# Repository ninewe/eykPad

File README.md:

# eykPad

<br><br>

<b>A multifunctional pad!</b>

This can be used for a timer, a sequence memory game, and other fun stuff!

This project is a compact PCB to play minigames with basically just LEDS and a 7-segment display, such as memory games. It can also act as a productive tool, such as the pomodoro timer. This project consists of 30 LEDs, (a 5 by 6 LED matrix). I used multiplexing to save GPIO pins.

It also has a 7 segment display, which is useful for displaying numbers, and that also expands the ideas of games I can make. I kept the buttons compact and minimal. There are only three buttons, where the main function of each of the buttons are: (go right), (switch color to pick), and (enter). This makes picking each light from the 30 LED way easier. 

# eykPad – bill of materials

> [!NOTE]
> This parts list is mirrored from [Half Life](https://halflife.hackclub.com). Editing it here will not change the platform's copy, and the next sync overwrites this file.

| Week | Tier | Parts funding |
| --- | --- | --- |
| Week 1 | Tier 1 | $30.00 |

| Part | What it's for | Qty | Unit | Total | Vendor |
| --- | --- | --- | --- | --- | --- |
| [150080RS75000](https://www.digikey.com/en/products/detail/w-rth-elektronik/150080RS75000/4489918?gclsrc=aw.ds&gad_source=1&gad_campaignid=20228387720&gbraid=0AAAAADrbLliBca_8CoGRREvYeSftxtPPf&gclid=Cj0KCQjwuJLWBhD_ARIsAIBcRUyE15Ih_jkTIqsu-BNJK-R_mNFNQNt-TY-f5ciIsWRtXfK5UMoC-bQaAiLSEALw_wcB) | Outputs of this project. (Red LED) | 12 | $0.19 | $2.28 | [DigiKey](https://www.digikey.com/en/products/detail/w-rth-elektronik/150080RS75000/4489918?gclsrc=aw.ds&gad_source=1&gad_campaignid=20228387720&gbraid=0AAAAADrbLliBca_8CoGRREvYeSftxtPPf&gclid=Cj0KCQjwuJLWBhD_ARIsAIBcRUyE15Ih_jkTIqsu-BNJK-R_mNFNQNt-TY-f5ciIsWRtXfK5UMoC-bQaAiLSEALw_wcB) |
| [150080BS75000](https://www.digikey.com/en/products/detail/würth-elektronik/150080BS75000/4489912?s=N4IgTCBcDaIIwFYAMSAcSBCBlA7MlIAugL5A) | Outputs of this project. (Blue LED) | 12 | $0.19 | $2.28 | [DigiKey](https://www.digikey.com/en/products/detail/würth-elektronik/150080BS75000/4489912?s=N4IgTCBcDaIIwFYAMSAcSBCBlA7MlIAugL5A) |
| [150080YS75000](https://www.digikey.com/en/products/detail/würth-elektronik/150080YS75000/4489927?s=N4IgTCBcDaIIwFYAMSAcSCaBlA7MlIAugL5A) | Outputs of this project. (Yellow LED) | 12 | $0.19 | $2.28 | [DigiKey](https://www.digikey.com/en/products/detail/würth-elektronik/150080YS75000/4489927?s=N4IgTCBcDaIIwFYAMSAcSCaBlA7MlIAugL5A) |
| [SC0915](https://www.digikey.com/en/products/detail/raspberry-pi/SC0915/13624793) | The microcontroller. (Raspberry Pi Pico) | 1 | $4.59 | $4.59 | [DigiKey](https://www.digikey.com/en/products/detail/raspberry-pi/SC0915/13624793) |
| [B3FS-1000P](https://www.digikey.com/en/products/detail/aratas-formerly-omron-components/B3FS-1000P/277812) | Inputs of this project. (The buttons) | 3 | $0.75 | $2.25 | [DigiKey](https://www.digikey.com/en/products/detail/aratas-formerly-omron-components/B3FS-1000P/277812) |
| [RC0603FR-10330RL](https://www.digikey.com/en/products/detail/yageo/rc0603fr-10330rl/13694144?_gl=1*120rrj8*_up*MQ..*_gs*MQ..&gclid=Cj0KCQjwxKfWBhDkARIsAMKwkNawzWwHylZYBSNY6BOOnOnXhfwnokVGLYxYg4FlJP0YA3B5n22bPJ0aAlVSEALw_wcB&gclsrc=aw.ds&gbraid=0AAAAADrbLlhJyPxw7Auh62ErySqGjBCvJ) | Resistors for this LED. (for RED, 330 OHMS) | 10 | $0.03 | $0.30 | [DigiKey](https://www.digikey.com/en/products/detail/yageo/rc0603fr-10330rl/13694144?_gl=1*120rrj8*_up*MQ..*_gs*MQ..&gclid=Cj0KCQjwxKfWBhDkARIsAMKwkNawzWwHylZYBSNY6BOOnOnXhfwnokVGLYxYg4FlJP0YA3B5n22bPJ0aAlVSEALw_wcB&gclsrc=aw.ds&gbraid=0AAAAADrbLlhJyPxw7Auh62ErySqGjBCvJ) |
| [LTS-6960HR](https://www.digikey.com/en/products/detail/liteon/LTS-6960HR/3199487) | Outputs of this project. (7 segment display) | 1 | $1.82 | $1.82 | [DigiKey](https://www.digikey.com/en/products/detail/liteon/LTS-6960HR/3199487) |
| [RC0603FR-10300RL](https://www.digikey.com/en/products/detail/yageo/RC0603FR-10300RL/14008461?gclsrc=aw.ds&gad_source=1&gad_campaignid=17335707486&gbraid=0AAAAADrbLlhJyPxw7Auh62ErySqGjBCvJ&gclid=Cj0KCQjwxKfWBhDkARIsAMKwkNawzWwHylZYBSNY6BOOnOnXhfwnokVGLYxYg4FlJP0YA3B5n22bPJ0aAlVSEALw_wcB) | Resistors for this LED. (for YELLOW, 300 OHMS) | 10 | $0.03 | $0.30 | [DigiKey](https://www.digikey.com/en/products/detail/yageo/RC0603FR-10300RL/14008461?gclsrc=aw.ds&gad_source=1&gad_campaignid=17335707486&gbraid=0AAAAADrbLlhJyPxw7Auh62ErySqGjBCvJ&gclid=Cj0KCQjwxKfWBhDkARIsAMKwkNawzWwHylZYBSNY6BOOnOnXhfwnokVGLYxYg4FlJP0YA3B5n22bPJ0aAlVSEALw_wcB) |
| [RC0603FR-0775RL](https://www.digikey.com/en/products/detail/yageo/RC0603FR-0775RL/727377?gclsrc=aw.ds&gad_source=1&gad_campaignid=17335707486&gbraid=0AAAAADrbLlhJyPxw7Auh62ErySqGjBCvJ&gclid=Cj0KCQjwxKfWBhDkARIsAMKwkNYsVzW8jDgrS64-7hHOIiOrCPiaaJvFeVMSugW8Nx8k4qDhcNRlPbUaAuaSEALw_wcB) | Resistors for this LED. (for BLUE, 75 OHMS) | 10 | $0.03 | $0.30 | [DigiKey](https://www.digikey.com/en/products/detail/yageo/RC0603FR-0775RL/727377?gclsrc=aw.ds&gad_source=1&gad_campaignid=17335707486&gbraid=0AAAAADrbLlhJyPxw7Auh62ErySqGjBCvJ&gclid=Cj0KCQjwxKfWBhDkARIsAMKwkNYsVzW8jDgrS64-7hHOIiOrCPiaaJvFeVMSugW8Nx8k4qDhcNRlPbUaAuaSEALw_wcB) |
| [PCB Board (SHIPPING INCLUDED)](https://jlcpcb.com) | The main PCB board | 1 | $5.06 | $5.06 | [JCLPCB](https://jlcpcb.com) |
| **Parts subtotal** | — | — | — | **$21.46** | — |
| **Tax & shipping** | — | — | — | **$7.75** | — |
| **Total** | — | — | — | **$29.21** | — |

$0.79 left of the tier's funding.

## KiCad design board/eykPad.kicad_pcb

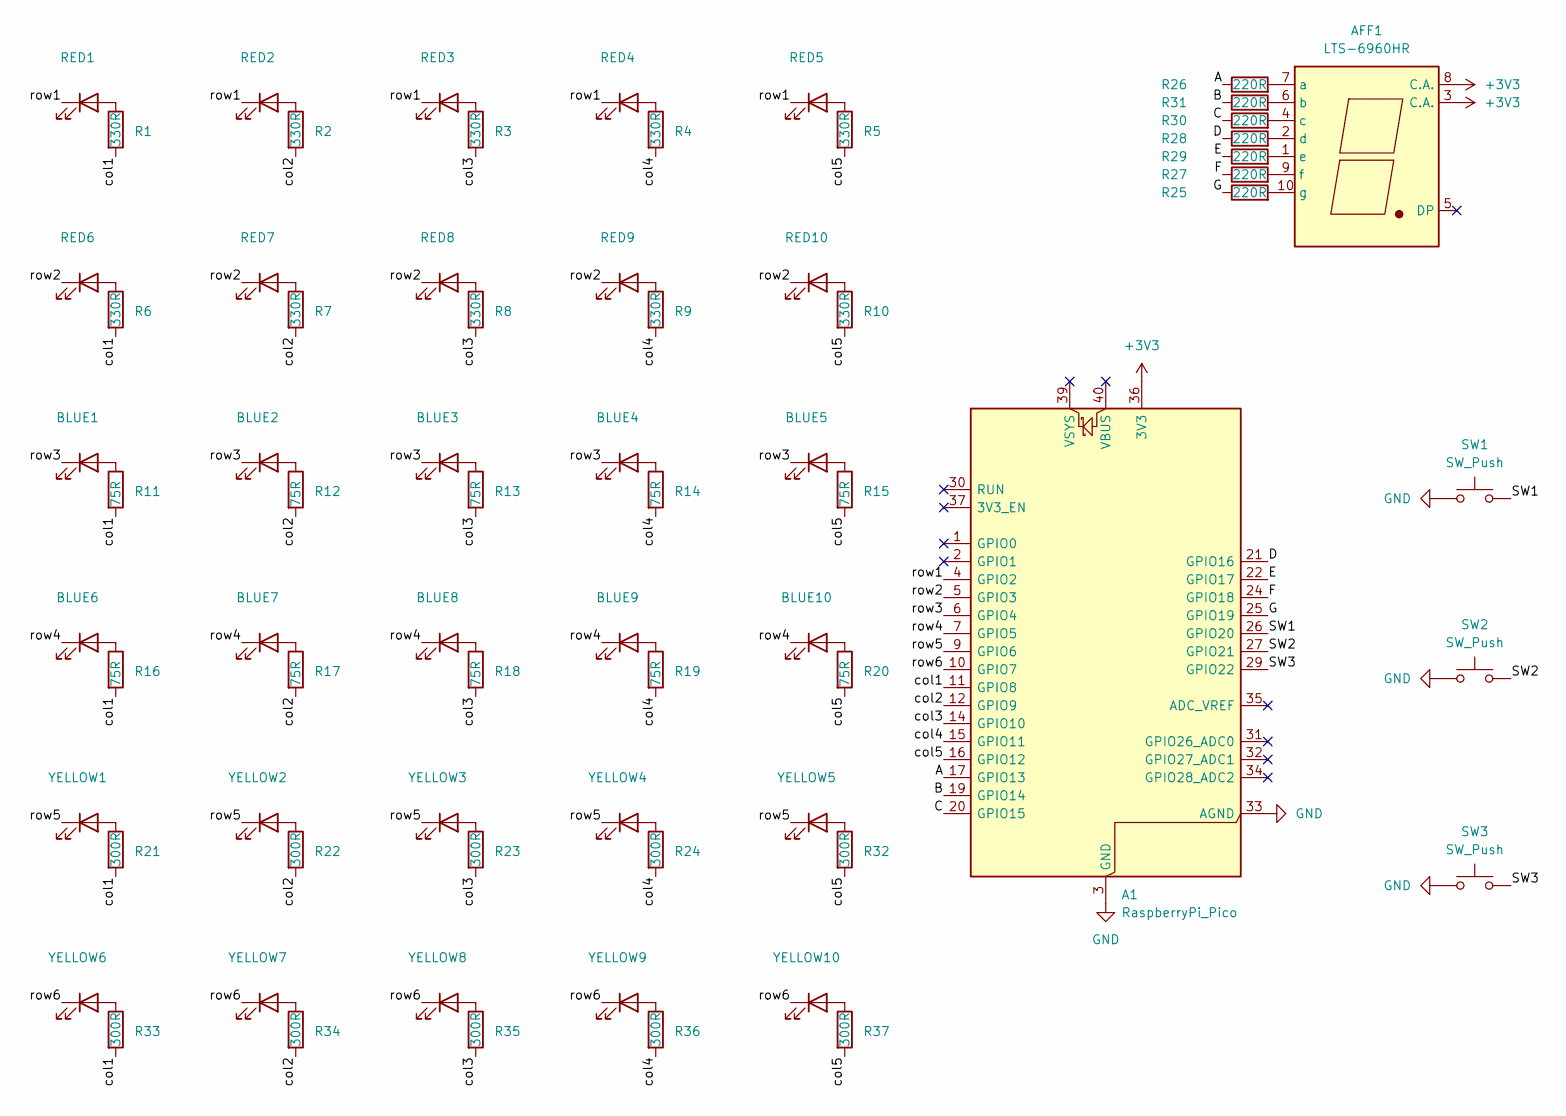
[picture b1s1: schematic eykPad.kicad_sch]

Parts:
A1: RaspberryPi_Pico; RaspberryPi_Pico_SMD_HandSolder
AFF1: LTS-6960HR; 7SegmentLED_LTS6760_LTS6780
BLUE1, BLUE2, BLUE3, BLUE4, BLUE5, BLUE6, BLUE7, BLUE8, BLUE9, BLUE10: 150080BS75000; LED_0805_2012Metric
R1, R2, R3, R4, R5, R6, R7, R8, R9, R10: 330R; R_0603_1608Metric
R11, R12, R13, R14, R15, R16, R17, R18, R19, R20: 75R; R_0603_1608Metric
R21, R22, R23, R24, R32, R33, R34, R35, R36, R37: 300R; R_0603_1608Metric
R25, R26, R27, R28, R29, R30, R31: 220R; R_0603_1608Metric
RED1, RED2, RED3, RED4, RED5, RED6, RED7, RED8, RED9, RED10: 150080RS75000; LED_0805_2012Metric
SW1, SW2, SW3: SW_Push; SW_SPST_Omron_B3FS-100xP
YELLOW1, YELLOW2, YELLOW3, YELLOW4, YELLOW5, YELLOW6, YELLOW7, YELLOW8, YELLOW9, YELLOW10: 150080YS75000; LED_0805_2012Metric

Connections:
+3V3: A1.36 (3V3), AFF1.3 (C.A.), AFF1.8 (C.A.)
/A: A1.17 (GPIO13), R26.1
/B: A1.19 (GPIO14), R31.1
/C: A1.20 (GPIO15), R30.1
/D: A1.21 (GPIO16), R28.1
/E: A1.22 (GPIO17), R29.1
/F: A1.24 (GPIO18), R27.1
/G: A1.25 (GPIO19), R25.1
/SW1: A1.26 (GPIO20), SW1.2
/SW2: A1.27 (GPIO21), SW2.2
/SW3: A1.29 (GPIO22), SW3.2
/col1: A1.11 (GPIO8), R1.2, R6.2, R11.2, R16.2, R21.2, R33.2
/col2: A1.12 (GPIO9), R2.2, R7.2, R12.2, R17.2, R22.2, R34.2
/col3: A1.14 (GPIO10), R3.2, R8.2, R13.2, R18.2, R23.2, R35.2
/col4: A1.15 (GPIO11), R4.2, R9.2, R14.2, R19.2, R24.2, R36.2
/col5: A1.16 (GPIO12), R5.2, R10.2, R15.2, R20.2, R32.2, R37.2
/row1: A1.4 (GPIO2), RED1.1 (K), RED2.1 (K), RED3.1 (K), RED4.1 (K), RED5.1 (K)
/row2: A1.5 (GPIO3), RED6.1 (K), RED7.1 (K), RED8.1 (K), RED9.1 (K), RED10.1 (K)
/row3: A1.6 (GPIO4), BLUE1.1 (K), BLUE2.1 (K), BLUE3.1 (K), BLUE4.1 (K), BLUE5.1 (K)
/row4: A1.7 (GPIO5), BLUE6.1 (K), BLUE7.1 (K), BLUE8.1 (K), BLUE9.1 (K), BLUE10.1 (K)
/row5: A1.9 (GPIO6), YELLOW1.1 (K), YELLOW2.1 (K), YELLOW3.1 (K), YELLOW4.1 (K), YELLOW5.1 (K)
/row6: A1.10 (GPIO7), YELLOW6.1 (K), YELLOW7.1 (K), YELLOW8.1 (K), YELLOW9.1 (K), YELLOW10.1 (K)
GND: A1.3 (GND), A1.8 (GND), A1.13 (GND), A1.18 (GND), A1.23 (GND), A1.28 (GND), A1.33 (AGND), A1.38 (GND), SW1.1, SW2.1, SW3.1
unnamed: AFF1.7 (a), R26.2
unnamed: AFF1.6 (b), R31.2
unnamed: AFF1.4 (c), R30.2
unnamed: AFF1.2 (d), R28.2
unnamed: AFF1.1 (e), R29.2
unnamed: AFF1.9 (f), R27.2
unnamed: AFF1.10 (g), R25.2
unnamed: BLUE1.2 (A), R11.1
unnamed: BLUE2.2 (A), R12.1
unnamed: BLUE3.2 (A), R13.1
unnamed: BLUE4.2 (A), R14.1
unnamed: BLUE5.2 (A), R15.1
unnamed: BLUE6.2 (A), R16.1
unnamed: BLUE7.2 (A), R17.1
unnamed: BLUE8.2 (A), R18.1
unnamed: BLUE9.2 (A), R19.1
unnamed: BLUE10.2 (A), R20.1
unnamed: R1.1, RED1.2 (A)
unnamed: R2.1, RED2.2 (A)
unnamed: R3.1, RED3.2 (A)
unnamed: R4.1, RED4.2 (A)
unnamed: R5.1, RED5.2 (A)
unnamed: R6.1, RED6.2 (A)
unnamed: R7.1, RED7.2 (A)
unnamed: R8.1, RED8.2 (A)
unnamed: R9.1, RED9.2 (A)
unnamed: R10.1, RED10.2 (A)
unnamed: R21.1, YELLOW1.2 (A)
unnamed: R22.1, YELLOW2.2 (A)
unnamed: R23.1, YELLOW3.2 (A)
unnamed: R24.1, YELLOW4.2 (A)
unnamed: R32.1, YELLOW5.2 (A)
unnamed: R33.1, YELLOW6.2 (A)
unnamed: R34.1, YELLOW7.2 (A)
unnamed: R35.1, YELLOW8.2 (A)
unnamed: R36.1, YELLOW9.2 (A)
unnamed: R37.1, YELLOW10.2 (A)

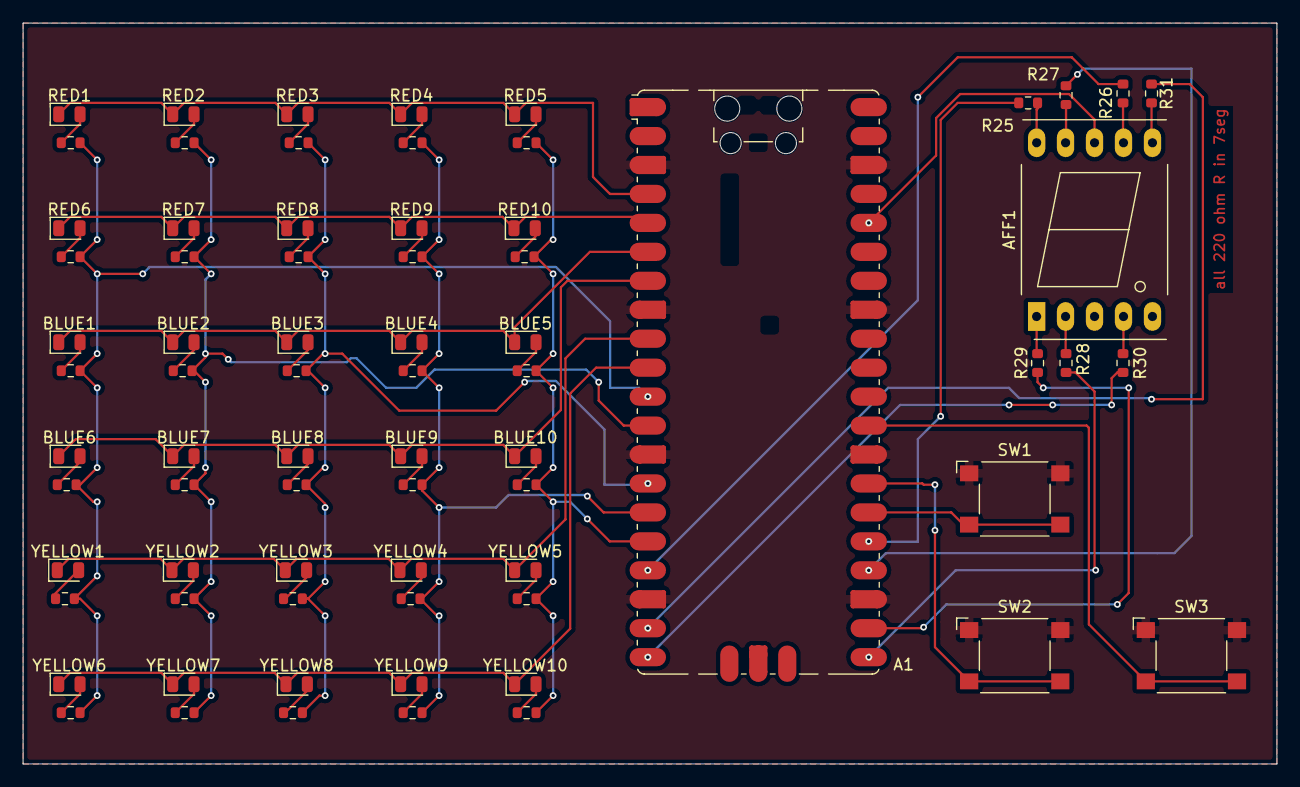
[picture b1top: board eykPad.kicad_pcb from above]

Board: 2 copper layers, 110.0 x 65.0 mm, 72 parts (0 on the bottom side), 60 nets.

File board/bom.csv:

Part,Qty,Unit,Total,Vendor,Link,Purpose
150080RS75000,12,$0.19,$2.28,DigiKey,https://www.digikey.com/en/products/detail/würth-elektronik/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,Outputs of this project. (Red LED)
150080BS75000,12,$0.19,$2.28,DigiKey,https://www.digikey.com/en/products/detail/würth-elektronik/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,Outputs of this project. (Blue LED)
150080YS75000,12,$0.19,$2.28,DigiKey,https://www.digikey.com/en/products/detail/würth-elektronik/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,Outputs of this project. (Yellow LED)
SC0915,1,$4.59,$4.59,DigiKey,https://www.digikey.com/en/products/detail/raspberry-pi/SC09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,The microcontroller. (Raspberry Pi Pico)
B3FS-1000P,3,$0.75,$2.25,DigiKey,https://www.digikey.com/en/products/detail/aratas-formerly-o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,Inputs of this project. (The buttons)
RC0603FR-10330RL,10,$0.03,$0.30,DigiKey,https://www.digikey.com/en/products/detail/yageo/rc0603fr-10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,"Resistors for this LED. (for Red, 330 OHMS)"
LTS-6960HR,1,$1.82,$1.82,DigiKey,https://www.digikey.com/en/products/detail/liteon/LTS-6960HR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,Outputs of this project. (7 segment display)
RC0603FR-10300RL,10,$0.03,$0.30,DigiKey,https://www.digikey.com/en/products/detail/yageo/RC0603FR-10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,"Resistors for this LED. (for Yellow, 300 OHMS)"
RC0603FR-0775RL,10,$0.03,$0.30,DigiKey,https://www.digikey.com/en/products/detail/yageo/RC0603FR-07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,"Resistors for this LED. (for Blue, 75 OHMS)"
PCB Board (SHIPPING INCLUDED),1,$5.06,$5.06,JCLPCB,-,The main PCB board.
Subtotal,-,-,$21.46,-,-,
Tarrifs & Shipping,-,-,$7.75,-,-,
Total,-,-,$29.21,-,-,
